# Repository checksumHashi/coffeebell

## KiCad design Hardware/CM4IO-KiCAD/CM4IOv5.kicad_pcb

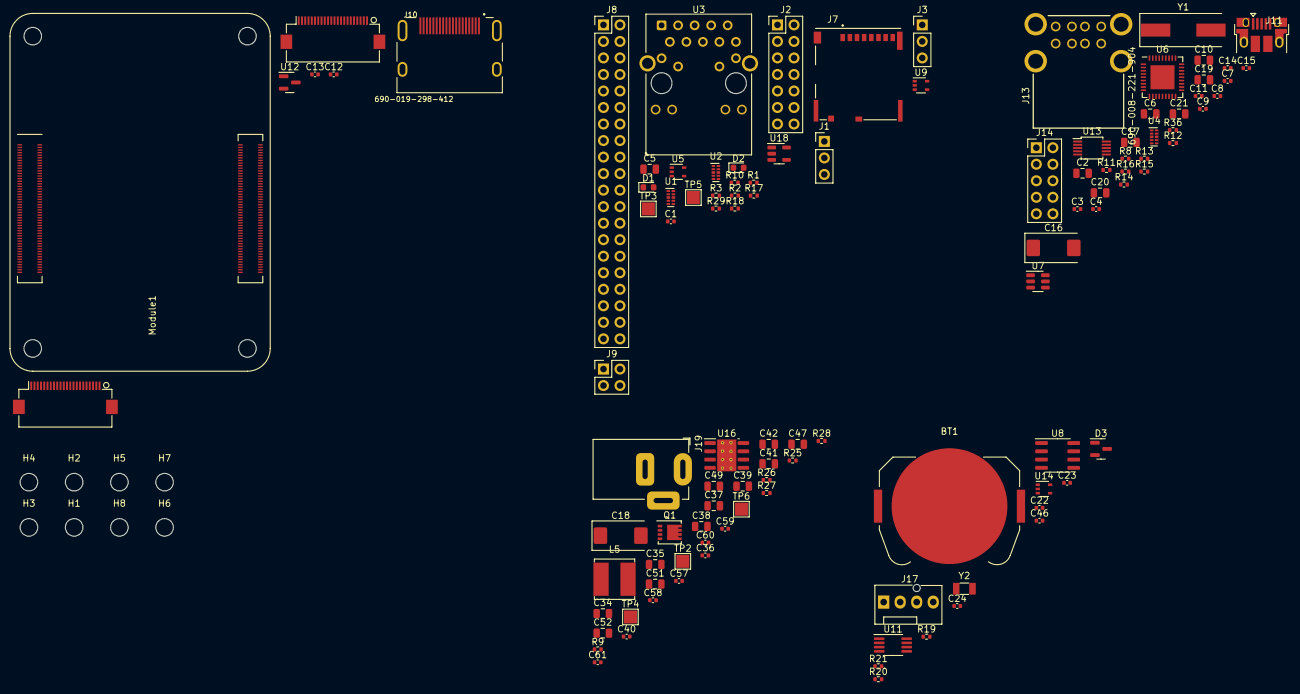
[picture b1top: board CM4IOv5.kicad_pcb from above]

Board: 2 copper layers, 117 parts (0 on the bottom side), 157 nets, no tracks yet.

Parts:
BT1: Battery_Cell; BatteryHolder_Keystone_3034_1x20mm
C1, C3, C4, C7, C11, C12, C13, C14, C15, C22, C23, C24, C40, C46, C57, C58: 100n; C_0402_1005Metric
C2, C5, C6, C10, C17, C19, C20, C21, C47, C49, C51, C52: 10u; C_0805_2012Metric
C8, C9: 27pF; C_0402_1005Metric
C16, C18: 100uF; CP_EIA-7343-31_Kemet-D
C34, C35, C37, C38, C39, C41, C42: 10u 35v; C_0805_2012Metric
C36: 100n 100v; C_0402_1005Metric
C59, C61: nf; C_0402_1005Metric
C60: 1.2nF; C_0402_1005Metric
D1: LED Red; LED_0603_1608Metric
D2: LED Green; LED_0603_1608Metric
D3: BAT54C-7-F; SOT-23
H1, H2, H3, H4, H5, H6, H7, H8: MountingHole; MountingHole_2.7mm_M2.5
J1, J3: Conn_01x03; PinHeader_1x03_P2.54mm_Vertical
J2: Conn_02x07_Odd_Even; PinHeader_2x07_P2.54mm_Vertical
J7: Micro_SD_Card_Det; SDCARD_MOLEX_503398-1892
J8: THD-20-R; PinHeader_2x20_P2.54mm_Vertical
J9: THD-02-R; PinHeader_2x02_P2.54mm_Vertical
J10: 690-019-298-412; EDAC 690-019-298-412
J11: USB_OTG; USB_Micro-B_EDAC_UCON00686
J13: 690-008-221-904; MOLEX_USB_67298-4090
J14: Conn_02x05_Odd_Even; PinHeader_2x05_P2.54mm_Vertical
J15, J16: Conn_01x22_Female; Hirose_FH12-22S-0.5SH_1x22-1MP_P0.50mm_Horizontal
J17: Molex 470531000; FanPinHeader_1x04_P2.54mm_Vertical
J19: Barrel_Jack; BarrelJack_Horizontal
L5: SRN6045TA-3R3Y; L_Bourns_SRN6045TA
Module1: ComputeModule4; Raspberry-Pi-4-Compute-Module
Q1: DMP3013SFV-7; Diodes_PowerDI3333-8
R1, R10: 1k; R_0402_1005Metric
R2, R3: 470R; R_0402_1005Metric
R8, R11, R28: 2.2K 1%; R_0402_1005Metric
R9: 10R; R_0402_1005Metric
R12, R13, R14, R16, R21: 36K 1%; R_0402_1005Metric
R15, R26, R27, R29: 12K 1%; R_0402_1005Metric
R17, R18: nf; R_0402_1005Metric
R19, R20: 510K 1%; R_0402_1005Metric
R25: 20K 1%; R_0402_1005Metric
R36: 15K 1%; R_0402_1005Metric
TP2, TP3, TP4, TP5, TP6: TestPoint; TestPoint_Pad_2.0x2.0mm
U1, U2, U4: TPD4EUSB30; USON-10_2.5x1.0mm_P0.5mm
U3: MagJack-A70-112-331N126; TRJG0926HENL
U5, U9, U14: 74LVC1G07SE-7; SOT-353_SC-70-5
U6: USB2514B-I/M2; QFN-36-1EP_6x6mm_P0.5mm_EP3.7x3.7mm
U7: AP22653W6; SOT-23-6
U8: PCF85063AT/AAZ; SOIC-8_3.9x4.9mm_P1.27mm
U11: EMC2301-1-ACZL-TR; MSOP-8_3x3mm_P0.65mm
U12: RT9742SNGV; SOT-23
U13: FSUSB42MUX; MSOP-10_3x3mm_P0.5mm
U16: AP64501SP-13; SOIC-8-1EP_3.9x4.9mm_P1.27mm_EP2.95x4.9mm_Mask2.71x3.4mm_Th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
U18: RT9742GGJ5; SOT-23-5
Y1: 24MHz; Crystal_SMD_HC49-SD
Y2: X32K768S301; Crystal_SMD_3215-2Pin_3.2x1.5mm

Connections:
/+3.3v: C3.1, C4.1, C6.1, C7.1, C10.1, C11.1, C14.1, C15.1, C23.1, D1.2 (A), D2.2 (A), D3.2, J8.1, J8.17, Module1.84 (+3.3v_(Output)), Module1.86 (+3.3v_(Output)), R17.1, R21.2, R29.1, U3.15 (LEDG_A), U3.17 (LEDY_A), U5.5 (VCC), U6.5 (VDDA33), U6.10 (VDDA33), U6.15 (VDD33), U6.23 (VDD33), U6.27 (VBUS_DET), U6.29 (VDDA33), U6.36 (VDDA33), U11.3 (VDD), U13.1 (VCC), U18.5 (IN)
/+5v: C2.1, C12.1, C18.1, C22.1, C47.1, C49.1, C51.1, C52.1, C61.1, J8.2, J8.4, L5.2, Module1.77 (+5v_(Input)), Module1.79 (+5v_(Input)), Module1.81 (+5v_(Input)), Module1.83 (+5v_(Input)), Module1.85 (+5v_(Input)), Module1.87 (+5v_(Input)), R19.2, R20.2, R27.1, TP4.1, U7.1 (IN), U9.5 (VCC), U12.1 (IN), U14.5 (VCC)
/+12v: C34.1, C35.1, C37.1, C38.1, C39.1, C40.1, C41.1, C42.1, J17.2, Q1.1 (S), Q1.2 (S), Q1.3 (S), TP2.1, U16.2 (VIN), U16.3 (EN)
/CM4_GPIO ( Ethernet, GPIO, SDCARD)/+1.8v: Module1.88 (+1.8v_(Output)), Module1.90 (+1.8v_(Output))
/CM4_GPIO ( Ethernet, GPIO, SDCARD)/AIN0: J2.5, Module1.96 (AnalogIP0)
/CM4_GPIO ( Ethernet, GPIO, SDCARD)/AIN1: J2.6, Module1.94 (AnalogIP1)
/CM4_GPIO ( Ethernet, GPIO, SDCARD)/BT_nDis: J3.3, Module1.91 (BT_nDisable)
/CM4_GPIO ( Ethernet, GPIO, SDCARD)/EEPROM_nWP: J2.4, Module1.20 (EEPROM_nWP)
/CM4_GPIO ( Ethernet, GPIO, SDCARD)/ETH_LEDG: Module1.17 (Ethernet_nLED2(3.3v)), R2.2
/CM4_GPIO ( Ethernet, GPIO, SDCARD)/ETH_LEDY: Module1.15 (Ethernet_nLED3(3.3v)), R3.2
/CM4_GPIO ( Ethernet, GPIO, SDCARD)/GLOBAL_EN: J1.1, J2.14, Module1.99 (Global_EN), U14.4
/CM4_GPIO ( Ethernet, GPIO, SDCARD)/GPIO2: J8.3, Module1.58 (GPIO2)
/CM4_GPIO ( Ethernet, GPIO, SDCARD)/GPIO3: J8.5, Module1.56 (GPIO3)
/CM4_GPIO ( Ethernet, GPIO, SDCARD)/GPIO4: J8.7, Module1.54 (GPIO4)
/CM4_GPIO ( Ethernet, GPIO, SDCARD)/GPIO5: J8.29, Module1.34 (GPIO5)
/CM4_GPIO ( Ethernet, GPIO, SDCARD)/GPIO6: J8.31, Module1.30 (GPIO6)
/CM4_GPIO ( Ethernet, GPIO, SDCARD)/GPIO7: J8.26, Module1.37 (GPIO7)
/CM4_GPIO ( Ethernet, GPIO, SDCARD)/GPIO8: J8.24, Module1.39 (GPIO8)
/CM4_GPIO ( Ethernet, GPIO, SDCARD)/GPIO9: J8.21, Module1.40 (GPIO9)
/CM4_GPIO ( Ethernet, GPIO, SDCARD)/GPIO10: J8.19, Module1.44 (GPIO10)
/CM4_GPIO ( Ethernet, GPIO, SDCARD)/GPIO11: J8.23, Module1.38 (GPIO11)
/CM4_GPIO ( Ethernet, GPIO, SDCARD)/GPIO12: J8.32, Module1.31 (GPIO12)
/CM4_GPIO ( Ethernet, GPIO, SDCARD)/GPIO13: J8.33, Module1.28 (GPIO13)
/CM4_GPIO ( Ethernet, GPIO, SDCARD)/GPIO14: J8.8, Module1.55 (GPIO14)
/CM4_GPIO ( Ethernet, GPIO, SDCARD)/GPIO15: J8.10, Module1.51 (GPIO15)
/CM4_GPIO ( Ethernet, GPIO, SDCARD)/GPIO16: J8.36, Module1.29 (GPIO16)
/CM4_GPIO ( Ethernet, GPIO, SDCARD)/GPIO17: J8.11, Module1.50 (GPIO17)
/CM4_GPIO ( Ethernet, GPIO, SDCARD)/GPIO18: J8.12, Module1.49 (GPIO18)
/CM4_GPIO ( Ethernet, GPIO, SDCARD)/GPIO19: J8.35, Module1.26 (GPIO19)
/CM4_GPIO ( Ethernet, GPIO, SDCARD)/GPIO20: J8.38, Module1.27 (GPIO20)
/CM4_GPIO ( Ethernet, GPIO, SDCARD)/GPIO21: J8.40, Module1.25 (GPIO21)
/CM4_GPIO ( Ethernet, GPIO, SDCARD)/GPIO22: J8.15, Module1.46 (GPIO22)
/CM4_GPIO ( Ethernet, GPIO, SDCARD)/GPIO23: J8.16, Module1.47 (GPIO23)
/CM4_GPIO ( Ethernet, GPIO, SDCARD)/GPIO24: J8.18, Module1.45 (GPIO24)
/CM4_GPIO ( Ethernet, GPIO, SDCARD)/GPIO25: J8.22, Module1.41 (GPIO25)
/CM4_GPIO ( Ethernet, GPIO, SDCARD)/GPIO26: J8.37, Module1.24 (GPIO26)
/CM4_GPIO ( Ethernet, GPIO, SDCARD)/GPIO27: J8.13, Module1.48 (GPIO27)
/CM4_GPIO ( Ethernet, GPIO, SDCARD)/ID_SC: J8.28, Module1.35 (ID_SC)
/CM4_GPIO ( Ethernet, GPIO, SDCARD)/ID_SD: J8.27, Module1.36 (ID_SD)
/CM4_GPIO ( Ethernet, GPIO, SDCARD)/RUN_PG: J1.3, Module1.92 (RUN_PG), U9.2
/CM4_GPIO ( Ethernet, GPIO, SDCARD)/Reserved: Module1.76 (Reserved), R18.1
/CM4_GPIO ( Ethernet, GPIO, SDCARD)/SD_CLK: J7.5 (CLK), Module1.57 (SD_CLK)
/CM4_GPIO ( Ethernet, GPIO, SDCARD)/SD_CMD: J7.3 (CMD), Module1.62 (SD_CMD)
/CM4_GPIO ( Ethernet, GPIO, SDCARD)/SD_DAT0: J7.7 (DAT0), Module1.63 (SD_DAT0)
/CM4_GPIO ( Ethernet, GPIO, SDCARD)/SD_DAT1: J7.8 (DAT1), Module1.67 (SD_DAT1)
/CM4_GPIO ( Ethernet, GPIO, SDCARD)/SD_DAT2: J7.1 (DAT2), Module1.69 (SD_DAT2)
/CM4_GPIO ( Ethernet, GPIO, SDCARD)/SD_DAT3: J7.2 (DAT3/CD), Module1.61 (SD_DAT3)
/CM4_GPIO ( Ethernet, GPIO, SDCARD)/SD_PWR: C5.1, J7.4 (VDD), U18.1 (OUT)
/CM4_GPIO ( Ethernet, GPIO, SDCARD)/SD_PWR_ON: Module1.75 (SD_PWR_ON), R29.2, U18.4 (EN)
/CM4_GPIO ( Ethernet, GPIO, SDCARD)/SYNC_IN: J2.8, Module1.16 (Ethernet_SYNC_IN(1.8v))
/CM4_GPIO ( Ethernet, GPIO, SDCARD)/SYNC_OUT: J2.9, Module1.18 (Ethernet_SYNC_OUT(1.8v))
/CM4_GPIO ( Ethernet, GPIO, SDCARD)/TR0_TAP: J9.3, U3.11 (VC1)
/CM4_GPIO ( Ethernet, GPIO, SDCARD)/TR1_TAP: J9.1, U3.12 (VC2)
/CM4_GPIO ( Ethernet, GPIO, SDCARD)/TR2_TAP: J9.2, U3.13 (VC3)
/CM4_GPIO ( Ethernet, GPIO, SDCARD)/TR3_TAP: J9.4, U3.14 (VC4)
/CM4_GPIO ( Ethernet, GPIO, SDCARD)/TRD0_N: Module1.10 (Ethernet_Pair0_N), U2.4 (D2+), U2.7, U3.2 (TRD0-)
/CM4_GPIO ( Ethernet, GPIO, SDCARD)/TRD0_P: Module1.12 (Ethernet_Pair0_P), U2.5 (D2-), U2.6, U3.1 (TRD0+)
/CM4_GPIO ( Ethernet, GPIO, SDCARD)/TRD1_N: Module1.6 (Ethernet_Pair1_N), U2.2 (D1-), U2.9, U3.6 (TRD1-)
/CM4_GPIO ( Ethernet, GPIO, SDCARD)/TRD1_P: Module1.4 (Ethernet_Pair1_P), U2.1 (D1+), U2.10, U3.3 (TRD1+)
/CM4_GPIO ( Ethernet, GPIO, SDCARD)/TRD2_N: Module1.9 (Ethernet_Pair2_N), U1.4 (D2+), U1.7, U3.8 (TRD2-)
/CM4_GPIO ( Ethernet, GPIO, SDCARD)/TRD2_P: Module1.11 (Ethernet_Pair2_P), U1.5 (D2-), U1.6, U3.7 (TRD2+)
/CM4_GPIO ( Ethernet, GPIO, SDCARD)/TRD3_N: Module1.5 (Ethernet_Pair3_N), U1.2 (D1-), U1.9, U3.10 (TRD3-)
/CM4_GPIO ( Ethernet, GPIO, SDCARD)/TRD3_P: Module1.3 (Ethernet_Pair3_P), U1.1 (D1+), U1.10, U3.9 (TRD3+)
/CM4_GPIO ( Ethernet, GPIO, SDCARD)/TV_OUT: J2.11, Module1.111 (VDAC_COMP)
/CM4_GPIO ( Ethernet, GPIO, SDCARD)/WL_nDis: J3.1, Module1.89 (WL_nDisable)
/CM4_GPIO ( Ethernet, GPIO, SDCARD)/nPWR_LED: Module1.95 (nPI_LED_PWR), U5.2
/CM4_GPIO ( Ethernet, GPIO, SDCARD)/nRPIBOOT: J2.2, Module1.93 (nRPIBOOT)
/CM4_HighSpeed/+3.3v: J15.22, J16.22
/CM4_HighSpeed/DSI0_C_N: J15.8, Module1.169 (DSI0_C_N)
/CM4_HighSpeed/DSI0_C_P: J15.9, Module1.171 (DSI0_C_P)
/CM4_HighSpeed/DSI0_D0_N: J15.2, Module1.157 (DSI0_D0_N)
/CM4_HighSpeed/DSI0_D0_P: J15.3, Module1.159 (DSI0_D0_P)
/CM4_HighSpeed/DSI0_D1_N: J15.5, Module1.163 (DSI0_D1_N)
/CM4_HighSpeed/DSI0_D1_P: J15.6, Module1.165 (DSI0_D1_P)
/CM4_HighSpeed/DSI1_C_N: J16.8, Module1.187 (DSI1_C_N)
/CM4_HighSpeed/DSI1_C_P: J16.9, Module1.189 (DSI1_C_P)
/CM4_HighSpeed/DSI1_D0_N: J16.2, Module1.175 (DSI1_D0_N)
/CM4_HighSpeed/DSI1_D0_P: J16.3, Module1.177 (DSI1_D0_P)
/CM4_HighSpeed/DSI1_D1_N: J16.5, Module1.181 (DSI1_D1_N)
/CM4_HighSpeed/DSI1_D1_P: J16.6, Module1.183 (DSI1_D1_P)
/CM4_HighSpeed/DSI1_D2_N: J16.11, Module1.193 (DSI1_D2_N)
/CM4_HighSpeed/DSI1_D2_P: J16.12, Module1.195 (DSI1_D2_P)
/CM4_HighSpeed/DSI1_D3_N: J16.14, Module1.194 (DSI1_D3_N)
/CM4_HighSpeed/DSI1_D3_P: J16.15, Module1.196 (DSI1_D3_P)
/CM4_HighSpeed/HDMI1_CEC: J10.13 (CEC), Module1.149 (HDMI1_CEC)
/CM4_HighSpeed/HDMI1_CK_N: J10.12 (CK-), Module1.166 (HDMI1_CLK_N)
/CM4_HighSpeed/HDMI1_CK_P: J10.10 (CK+), Module1.164 (HDMI1_CLK_P)
/CM4_HighSpeed/HDMI1_D0_N: J10.9 (D0-), Module1.160 (HDMI1_TX0_N)
/CM4_HighSpeed/HDMI1_D0_P: J10.7 (D0+), Module1.158 (HDMI1_TX0_P)
/CM4_HighSpeed/HDMI1_D1_N: J10.6 (D1-), Module1.154 (HDMI1_TX1_N)
/CM4_HighSpeed/HDMI1_D1_P: J10.4 (D1+), Module1.152 (HDMI1_TX1_P)
/CM4_HighSpeed/HDMI1_D2_N: J10.3 (D2-), Module1.148 (HDMI1_TX2_N)
/CM4_HighSpeed/HDMI1_D2_P: J10.1 (D2+), Module1.146 (HDMI1_TX2_P)
/CM4_HighSpeed/HDMI1_HOTPLUG: J10.19 (HPD/HEAC-), Module1.143 (HDMI1_HOTPLUG)
/CM4_HighSpeed/HDMI1_SCL: J10.15 (SCL), Module1.147 (HDMI1_SCL)
/CM4_HighSpeed/HDMI1_SDA: J10.16 (SDA), Module1.145 (HDMI1_SDA)
/CM4_HighSpeed/HDMI_5v: C13.1, J10.18 (+5V), U12.2 (OUT)
/CM4_HighSpeed/USB2_N: Module1.103 (USB2_N), U13.4 (D_N)
/CM4_HighSpeed/USB2_P: Module1.105 (USB2_P), U13.3 (D_P)
/CM4_HighSpeed/USBOTG_ID: Module1.101 (USB_OTG_ID), R8.2, R11.1, U13.2 (SEL)
/RTC , Wakeup, FAN/SCL: Module1.80 (SCL0), U8.6 (SCL), U11.2 (SCL)
/RTC , Wakeup, FAN/SDA: Module1.82 (SDA0), U8.5 (SDA), U11.1 (SDA)
/RTC , Wakeup, FAN/nRTC_INT: C24.2, R19.1, U8.3 (~INT)
/USB2-HUB/HD1_N: J13.2 (D-`), U6.1 (USBDM_DN1/PRT_DIS_M1)
/USB2-HUB/HD1_P: J13.3 (D+`), U6.2 (USBDP_DN1/PRT_DIS_P1)
/USB2-HUB/HD2_N: J13.6 (D-), U6.3 (USBDM_DN2/PRT_DIS_M2)
/USB2-HUB/HD2_P: J13.7 (D+), U6.4 (USBDP_DN2/PRT_DIS_P2)
/USB2-HUB/HD3_N: J14.3, U6.6 (USBDM_DN3/PRT_DIS_M3)
/USB2-HUB/HD3_P: J14.5, U6.7 (USBDP_DN3/PRT_DIS_P3)
/USB2-HUB/HD4_N: J14.4, U6.8 (USBDM_DN4/PRT_DIS_M4)
/USB2-HUB/HD4_P: J14.6, U6.9 (USBDP_DN4/PRT_DIS_P4)
/USB2-HUB/PWR1: U6.12 (PRTPWR1/BC_EN1), U7.3 (EN)
/USB2-HUB/USBD_N: J11.2 (D-), U4.4 (D2+), U4.7, U13.8 (HSD1_M)
/USB2-HUB/USBD_P: J11.3 (D+), U4.5 (D2-), U4.6, U13.9 (HSD1_P)
/USB2-HUB/USBH_N: U6.30 (USBDM_UP), U13.6 (HSD0_M)
/USB2-HUB/USBH_P: U6.31 (USBDP_UP), U13.7 (HSD0_P)
/USB2-HUB/VBUS: C16.1, C17.1, C19.1, C20.1, C21.1, J13.1 (VBUS`), J13.5 (VBUS), J14.1, J14.2, U7.6 (OUT)
/USB2-HUB/nOCS1: U6.13 (OCS_N1), U6.17 (OCS_N2), U6.19 (OCS_N3), U6.21 (OCS_N4), U7.4 (nFault)
/nEXTRST: Module1.100 (nEXTRST), U6.26 (RESET_N)
GND: BT1.2 (-), C1.2, C2.2, C3.2, C4.2, C5.2, C6.2, C7.2, C8.2, C9.2, C10.2, C11.2, C12.2, C13.2, C14.2, C15.2, C16.2, C17.2, C18.2, C19.2, C20.2, C21.2, C22.2, C23.2, C34.2, C35.2, C36.2, C37.2, C38.2, C39.2, C41.2, C42.2, C46.2, C47.2, C49.2, C51.2, C52.2, C58.2, C59.2, C60.2, J1.2, J2.1, J2.3, J2.7, J2.10, J2.12, J3.2, J7.6 (VSS), J7.11 (SHIELD), J8.6, J8.9, J8.14, J8.20, J8.25, J8.30, J8.34, J8.39, J10.2 (D2S), J10.5 (D1S), J10.8 (D0S), J10.11 (CKS), J10.17 (GND), J10.SH1 (SH), J10.SH2 (SH), J10.SH3 (SH), J10.SH4 (SH), J11.5 (GND), J11.6 (Shield), J13.4 (GND`), J13.8 (GND), J13.MT1, J13.MT2, J13.MT3, J13.MT4, J14.7, J14.8, J15.1, J15.4, J15.7, J15.10, J15.13, J15.16, J15.19, J16.1, J16.4, J16.7, J16.10, J16.13, J16.16, J16.19, J17.1, J19.2, J19.3, Module1.1 (GND), Module1.2 (GND), Module1.7 (GND), Module1.8 (GND), Module1.13 (GND), Module1.14 (GND), Module1.22 (GND), Module1.23 (GND), Module1.32 (GND), Module1.33 (GND), Module1.42 (GND), Module1.43 (GND), Module1.52 (GND), Module1.53 (GND), Module1.59 (GND), Module1.60 (GND), Module1.65 (GND), Module1.66 (GND), Module1.71 (GND), Module1.74 (GND), Module1.98 (GND), Module1.107 (GND), Module1.108 (GND), Module1.113 (GND), Module1.114 (GND), Module1.119 (GND), Module1.120 (GND), Module1.125 (GND), Module1.126 (GND), Module1.131 (GND), Module1.132 (GND), Module1.137 (GND), Module1.138 (GND), Module1.144 (GND), Module1.150 (GND), Module1.155 (GND), Module1.156 (GND), Module1.161 (GND), Module1.162 (GND), Module1.167 (GND), Module1.168 (GND), Module1.173 (GND), Module1.174 (GND), Module1.179 (GND), Module1.180 (GND), Module1.185 (GND), Module1.186 (GND), Module1.191 (GND), Module1.192 (GND), Module1.197 (GND), Module1.198 (GND), R11.2, R12.2, R13.2, R14.2, R15.1, R16.2, R26.2, R28.2, R36.2, TP6.1, U1.3 (GND), U1.8 (GND), U2.3 (GND), U2.8 (GND), U3.19 (SHIELD), U3.20 (SHIELD), U4.3 (GND), U4.8 (GND), U5.3 (GND), U6.37 (VSS), U7.2 (GND), U8.4 (VSS), U9.3 (GND), U11.4 (GND), U12.3 (GND), U13.5 (GND), U13.10 (nOE), U14.3 (GND), U16.7 (GND), U16.9 (EP), U18.2 (GND)
unnamed: BT1.1 (+), D3.1
unnamed: C1.1, U3.4 (CT), U3.5 (CT)
unnamed: C8.1, U6.33 (XTALIN/CLKIN), Y1.1
unnamed: C9.1, U6.32 (XTALOUT), Y1.2
unnamed: C24.1, R20.1, U14.2
unnamed: C36.1, J19.1, Q1.5 (D)
unnamed: C40.2, Q1.4 (G), R26.1
unnamed: C46.1, D3.3, U8.8 (VDD)
unnamed: C57.1, R9.2
unnamed: C57.2, U16.1 (BST)
unnamed: C58.1, U16.4 (SS)
unnamed: C59.1, R25.1, U16.6 (COMP)
unnamed: C60.1, R25.2
unnamed: C61.2, R27.2, R28.1, U16.5 (FB)
unnamed: D1.1 (K), R10.1, TP5.1
unnamed: D2.1 (K), R1.1, TP3.1
unnamed: J2.13, U9.4
unnamed: J7.9 (DET_B), R18.2
unnamed: J7.10 (DET_A), R17.2
unnamed: J11.1 (VBUS), R8.1
unnamed: J17.3, R21.1, U11.6 (TACH)
unnamed: J17.4, U11.5 (PWM)
unnamed: L5.1, R9.1, U16.8 (SW)
unnamed: Module1.21 (PI_nLED_Activity), R1.2
unnamed: R2.1, U3.16 (LEDG_K)
unnamed: R3.1, U3.18 (LEDY_K)
unnamed: R10.2, U5.4
unnamed: R12.1, U6.24 (SCL/SMBCLK/CFG_SEL0)
unnamed: R13.1, U6.22 (SDA/SMBDATA/NON_REM1)
unnamed: R14.1, U6.28 (SUSP_IND/LOCAL_PWR/NON_REM0)
unnamed: R15.2, U6.35 (RBIAS)
unnamed: R16.1, U6.25 (HS_IND/CFG_SEL1)
unnamed: R36.1, U7.5 (ILIM)
unnamed: U4.1 (D1+), U4.10
unnamed: U4.2 (D1-), U4.9
unnamed: U8.1 (OSCI), Y2.2
unnamed: U8.2 (OSCO), Y2.1

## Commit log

2023-01-16 Reorganized
2023-01-17 Updated notes.txt
2023-01-21 Added cad files
2023-01-21 Reogranized, figured out pcb design, kinda, WIP
2023-01-21 Deleted Notes, useless now
2023-01-23 Who_the_fuck_knows.jpg
2023-02-01 Added some STL files for a case for the IO board
2023-06-03 added some files to be organized
2023-06-08 Added old software
2023-06-08 Removed useless stuff, reogranized
2023-06-08 test commit
2023-06-08 Created venv, added gunicorn config
2023-06-09 gunicorn and wsgi work, need to test apache sock connection
2023-06-09 wsgi and gunicorn work, test apache with sock
